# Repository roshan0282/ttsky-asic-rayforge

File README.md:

# How to build the c-implementation of the raytracer

**Option 1: Windows (build.bat)**
1. Ensure MSYS2 UCRT64 is installed at `C:\msys64\ucrt64` with SDL2 installed
2. Navigate to `c-implementation/` folder
3. Run `build.bat` to compile and launch the raytracer

**Option 2: CMake (cross-platform)**
1. Install CMake (3.16+) and SDL2
2. Navigate to `c-implementation/` folder
3. Create a build directory:
   ```bash
   mkdir build && cd build
   cmake ..
   cmake --build . --config Release
   ./raytracer  # or raytracer.exe on Windows
   ```

The raytracer renders a 640×480 scene using Q8.4 fixed-point math and displays it in an SDL2 window.

# How to use verilator-bench to see proper-implementation-no-uart in action
1. Edit `verilator-bench/config.sh`:
   - Set `VERILATOR_SOURCE_FOLDER` to `proper-implementation-no-uart`
   - Set `VERILATOR_TOP_MODULE` to `raytracer_simple`
2. In an MSYS2 UCRT64 terminal, navigate to `verilator-bench/`
3. Run `bash run.sh` to build and launch the raytracer in an SDL window
4. Make sure you have dependencies installed: Verilator, CMake, SDL2, etc.

# How to generate more scenes for the proper-implementation-no-uart
1. go to rayforge.ayannali.net to generate a new scene
2. copy this .sv file and place into scene_lut.sv in proper-implementation-no-uart
3. re-run verilator-bench to see the new scene in action

# Presentation

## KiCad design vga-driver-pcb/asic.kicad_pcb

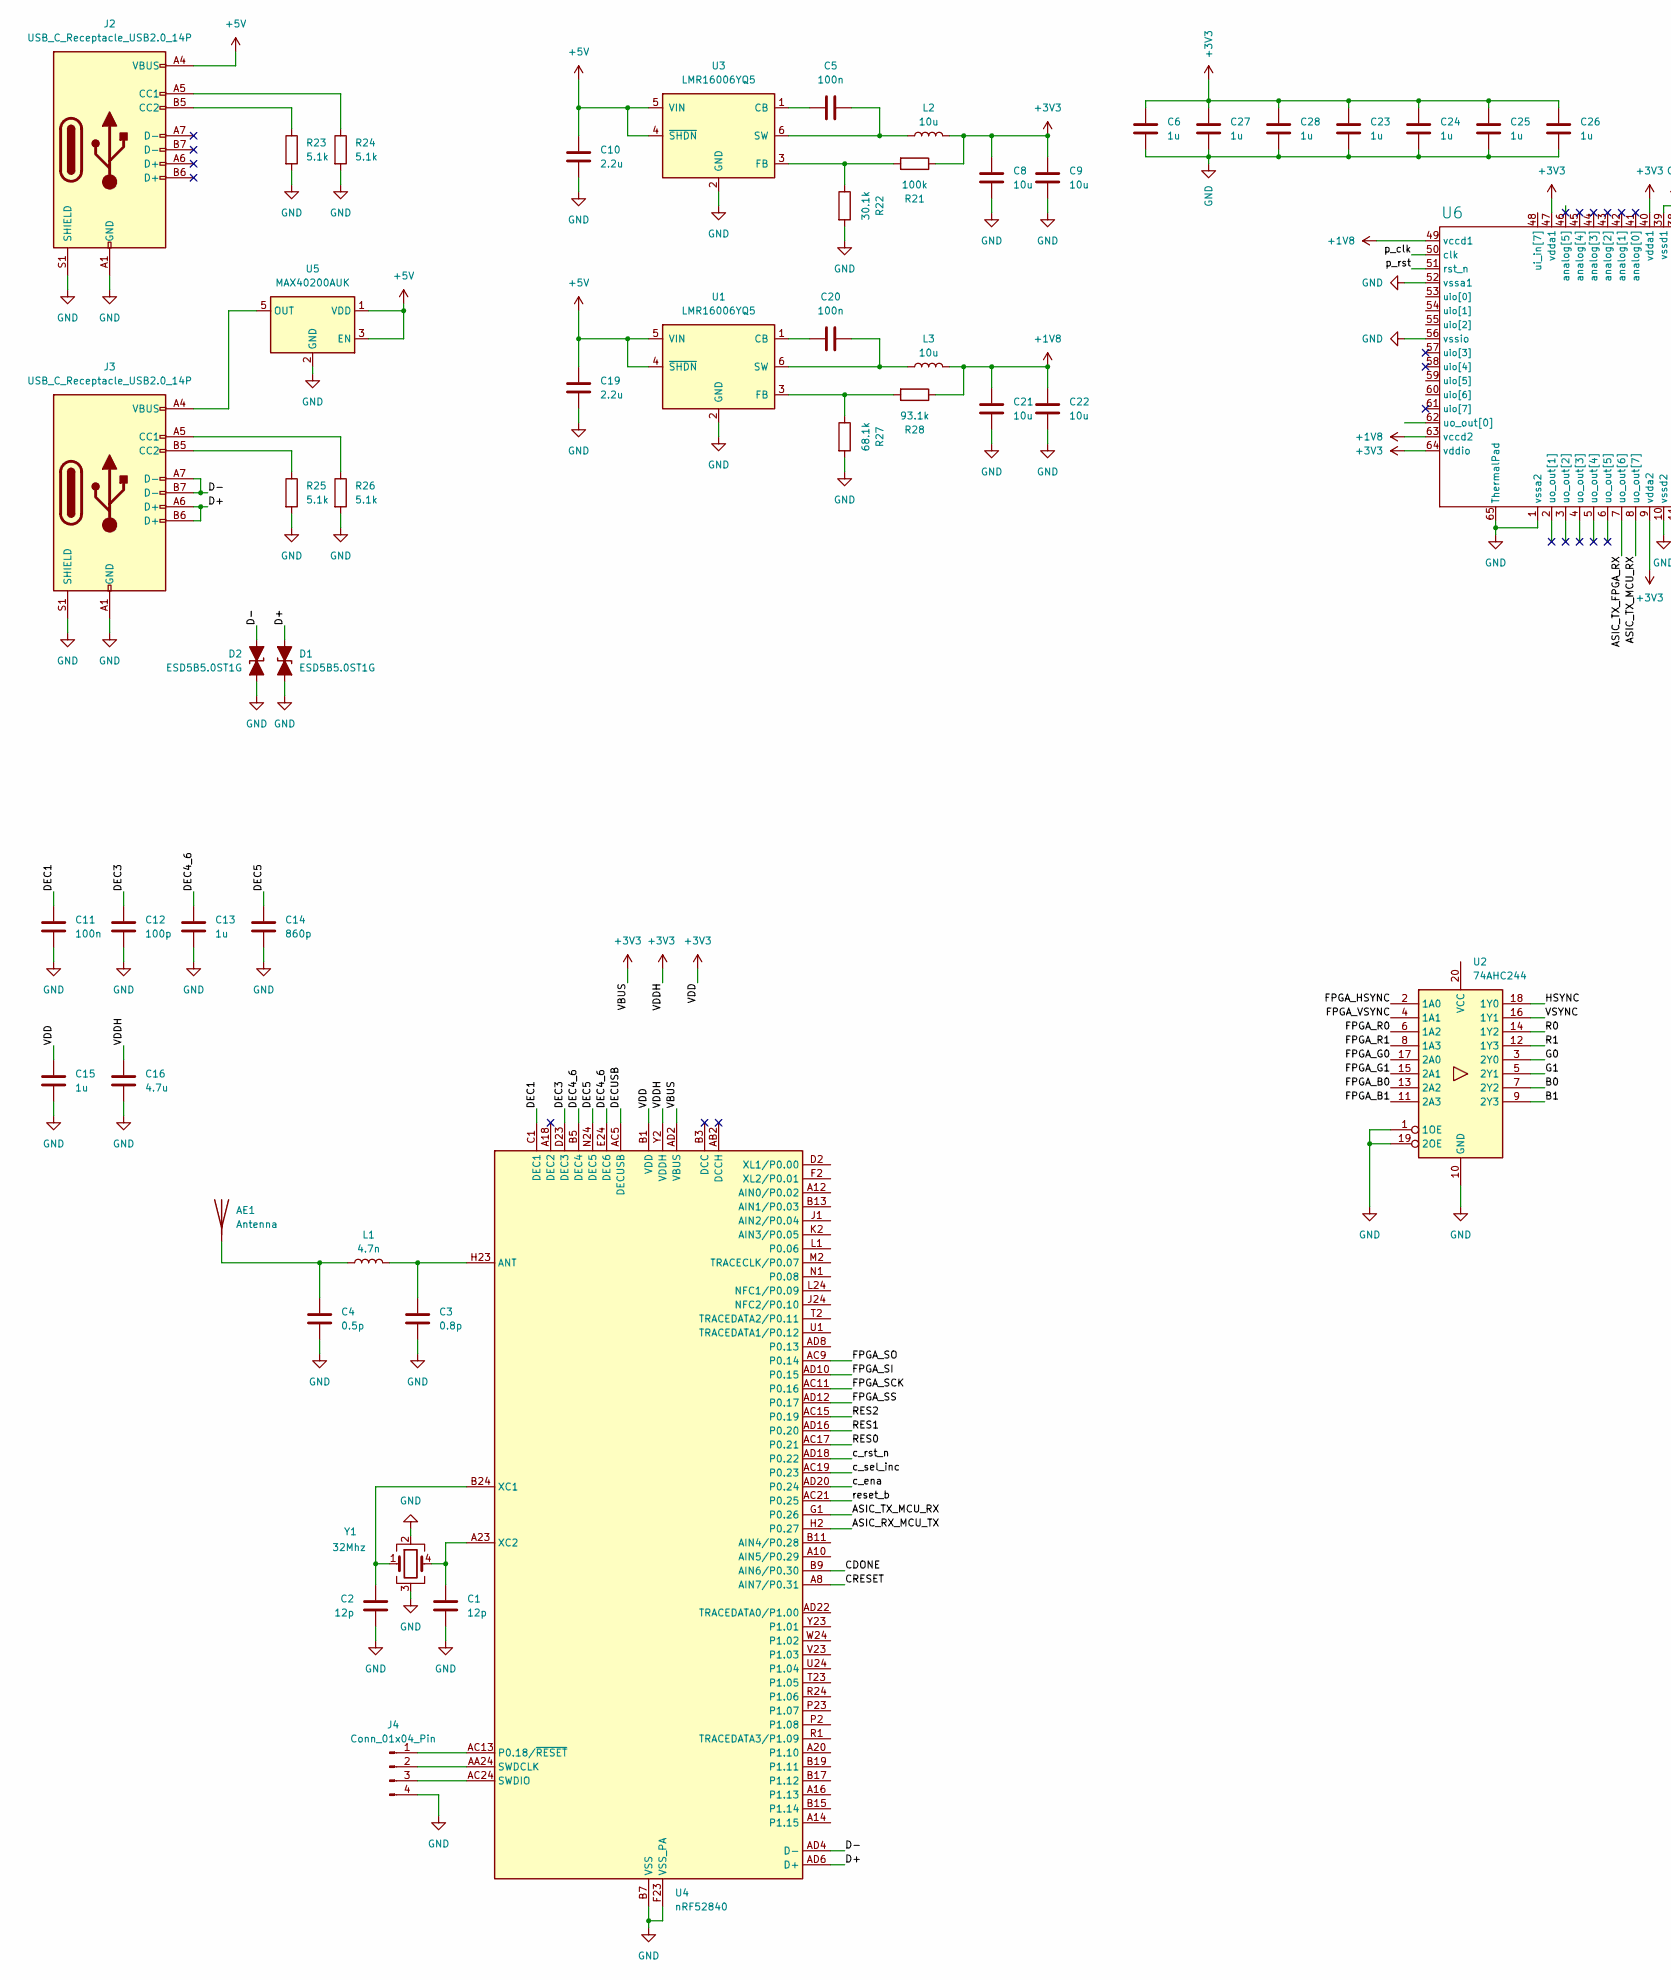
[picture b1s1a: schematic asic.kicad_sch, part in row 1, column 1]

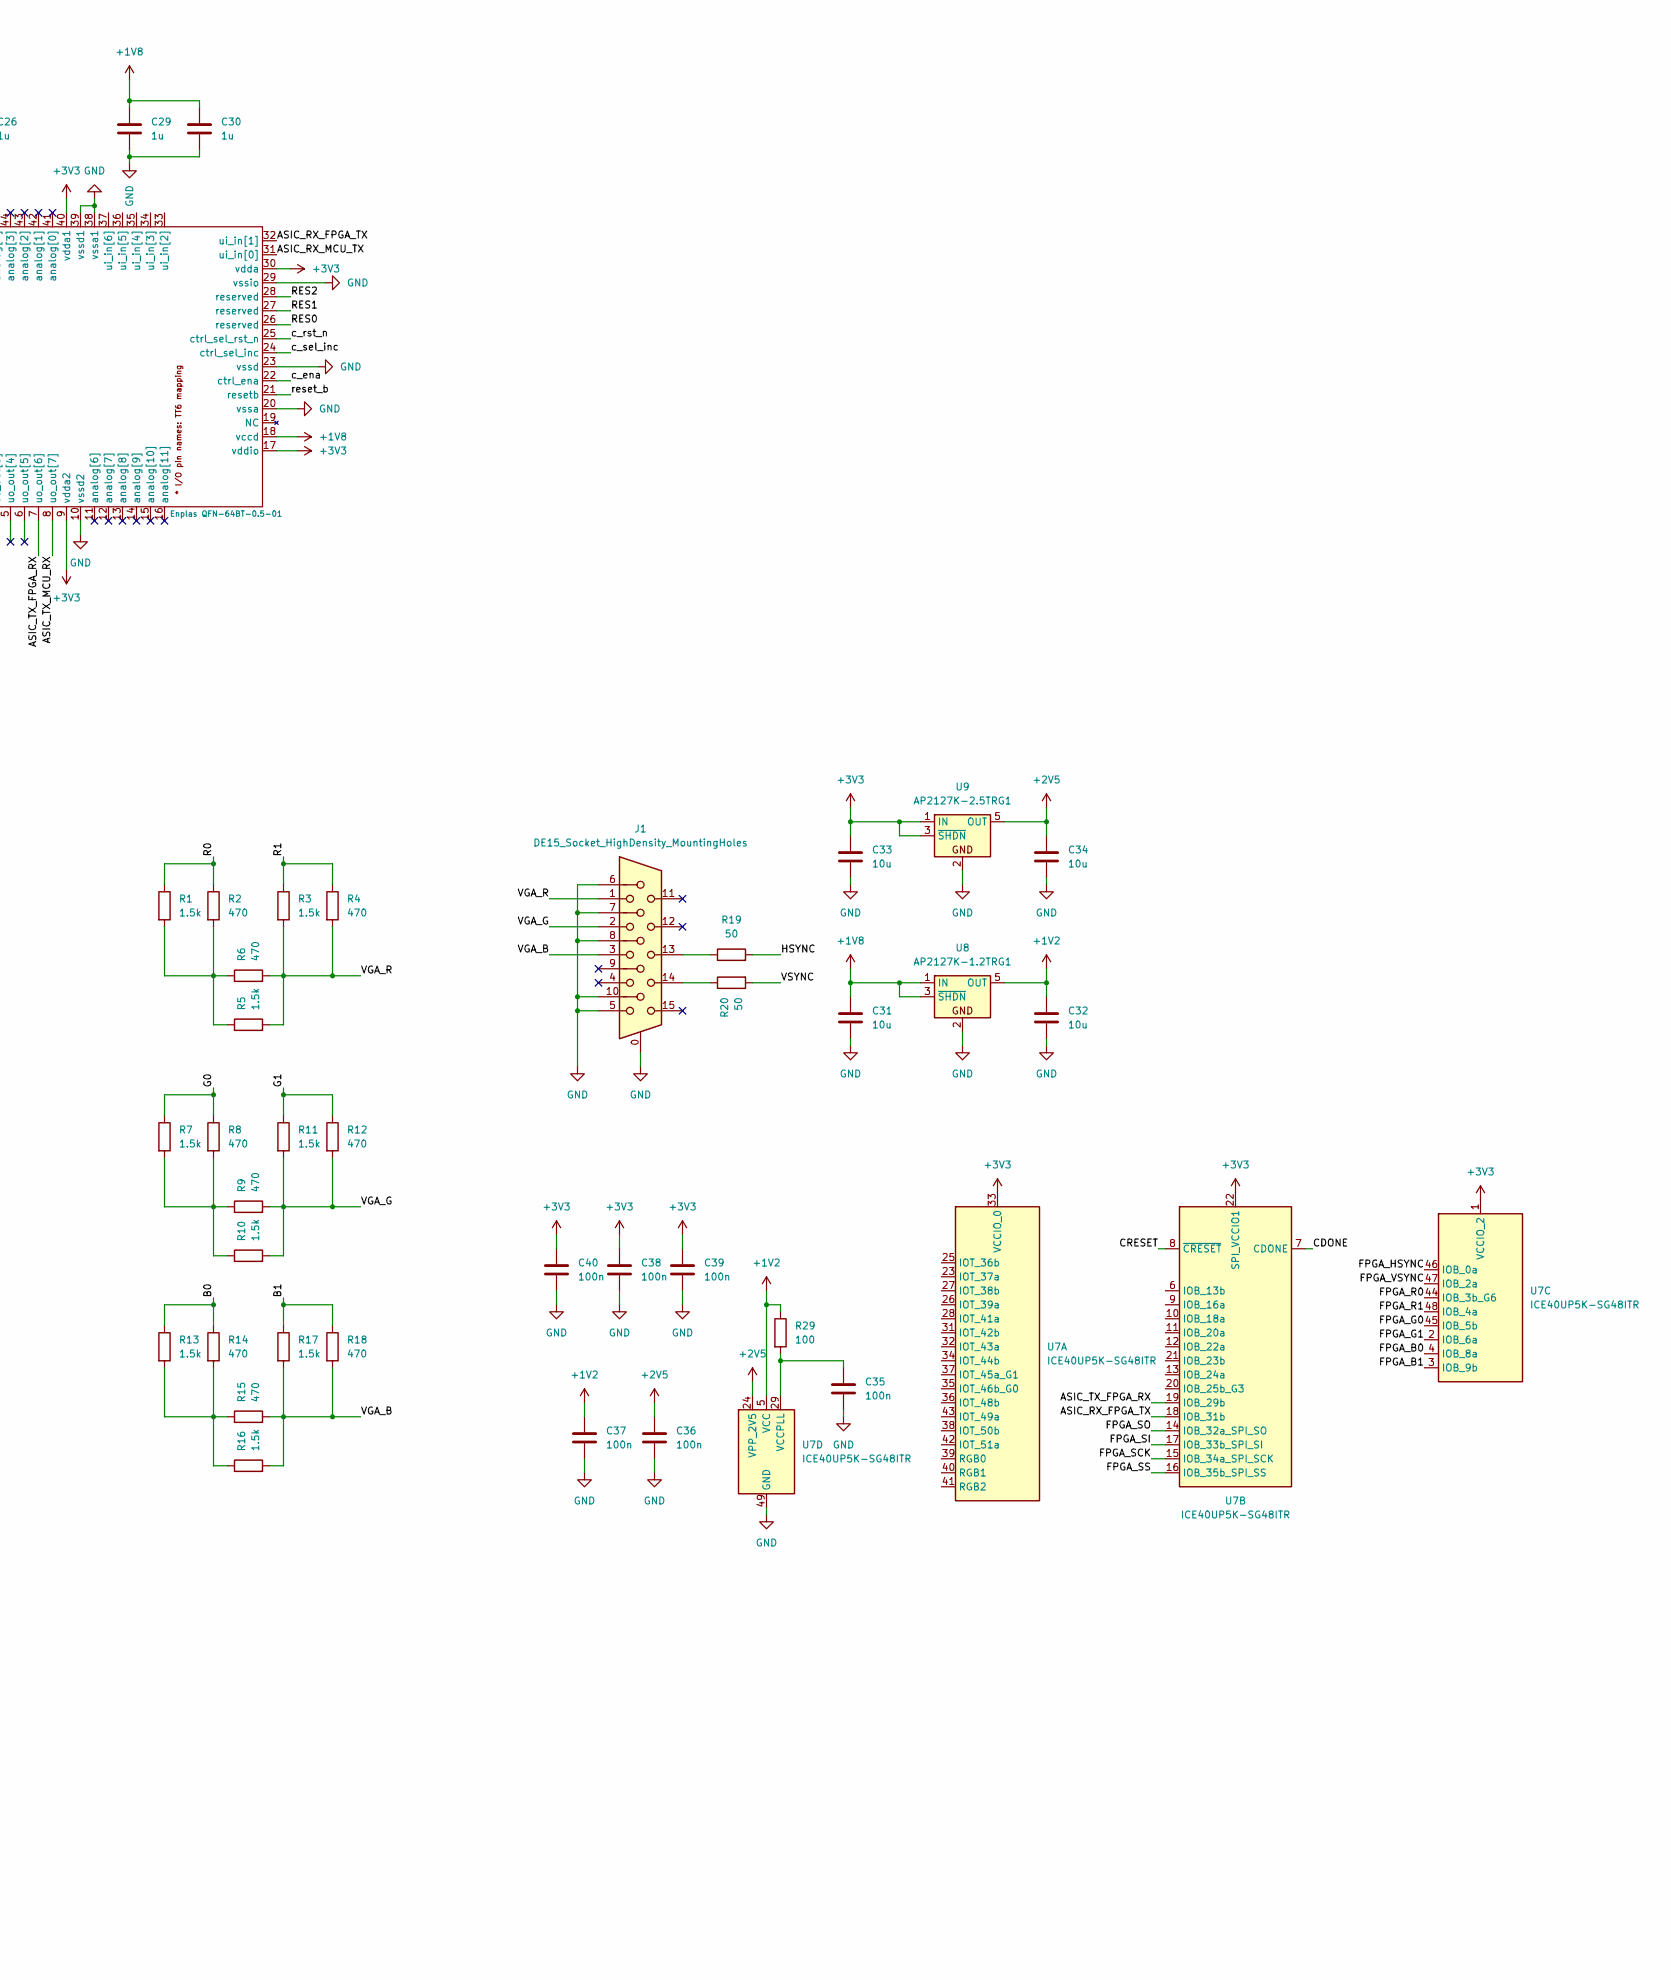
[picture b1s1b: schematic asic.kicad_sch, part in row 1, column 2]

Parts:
AE1: Antenna; Texas_SWRA117D_2.4GHz_Left
C1, C2: 12p; C_0402_1005Metric
C3: 0.8p; C_0402_1005Metric
C4: 0.5p; C_0402_1005Metric
C5, C11, C20, C35, C36, C37, C38, C39, C40: 100n; C_0402_1005Metric
C6, C13, C15, C23, C24, C25, C26, C27, C28, C29, C30: 1u; C_0402_1005Metric
C8, C9, C21, C22, C31, C32, C33, C34: 10u; C_0603_1608Metric
C10, C19: 2.2u; C_0603_1608Metric
C12: 100p; C_0402_1005Metric
C14: 860p; C_0402_1005Metric
C16: 4.7u; C_0402_1005Metric
D1, D2: ESD5B5.0ST1G; D_SOD-523
J1: DE15_Socket_HighDensity_MountingHoles; DSUB-15_Pins_Horizontal_P2.77x2.84mm_EdgePinOffset14.56mm_H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
J2, J3: USB_C_Receptacle_USB2.0_14P; USB_C_Receptacle_GCT_USB4105-xx-A_16P_TopMnt_Horizontal
J4: Conn_01x04_Pin; PinHeader_1x04_P1.00mm_Vertical_SMD_Pin1Left
L1: 4.7n; L_0402_1005Metric
L2, L3: 10u; L_0805_2012Metric
R1, R3, R5, R7, R10, R11, R13, R16, R17: 1.5k; R_0402_1005Metric
R2, R4, R6, R8, R9, R12, R14, R15, R18: 470; R_0402_1005Metric
R19, R20: 50; R_0402_1005Metric
R21: 100k; R_0402_1005Metric
R22: 30.1k; R_0402_1005Metric
R23, R24, R25, R26: 5.1k; R_0402_1005Metric
R27: 68.1k; R_0402_1005Metric
R28: 93.1k; R_0402_1005Metric
R29: 100; R_0402_1005Metric
U1, U3: LMR16006YQ5; SOT-23-6
U2: 74AHC244; WQFN-20-1EP_2.5x4.5mm_P0.5mm_EP1x2.9mm
U4: nRF52840; Nordic_AQFN-73-1EP_7x7mm_P0.5mm
U5: MAX40200AUK; SOT-23-5
U6: Enplas QFN-64BT-0.5-01; QFN-64-1EP_9x9mm_P0.5mm_EP7.3x7.3mm; MPN QFN-64BT-0.5-01
U7: ICE40UP5K-SG48ITR; QFN-48-1EP_7x7mm_P0.5mm_EP5.6x5.6mm
U8: AP2127K-1.2TRG1; SOT-23-5
U9: AP2127K-2.5TRG1; SOT-23-5
Y1: 32Mhz; Crystal_SMD_1210-4Pin_1.2x1.0mm

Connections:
+1V2: C32.2, C37.1, R29.1, U7.5 (VCC), U7.30 (VCC), U8.5 (OUT)
+1V8: C21.2, C22.2, C29.1, C30.1, C31.2, L3.2, R28.1, U6.18 (vccd), U6.49 (vccd1), U6.63 (vccd2), U8.1 (IN), U8.3 (~SHDN)
+2V5: C34.2, C36.1, U7.24 (VPP_2V5), U9.5 (OUT)
+3V3: C6.1, C8.2, C9.2, C15.1, C16.1, C23.1, C24.1, C25.1, C26.1, C27.1, C28.1, C33.2, C38.1, C39.1, C40.1, L2.2, R21.1, U4.A22 (VDD), U4.AD2 (VBUS), U4.AD14 (VDD), U4.AD23 (VDD), U4.B1 (VDD), U4.W1 (VDD), U4.Y2 (VDDH), U6.9 (vdda2), U6.17 (vddio), U6.30 (vdda), U6.40 (vdda1), U6.47 (vdda1), U6.64 (vddio), U7.1 (VCCIO_2), U7.22 (SPI_VCCIO1), U7.33 (VCCIO_0), U9.1 (IN), U9.3 (~SHDN)
+5V: C10.2, C19.2, J2.A4 (VBUS), J2.A9 (VBUS), J2.B4 (VBUS), J2.B9 (VBUS), U1.4 (~SHDN), U1.5 (VIN), U3.4 (~SHDN), U3.5 (VIN), U5.1 (VDD), U5.3 (EN)
/ASIC_RX_FPGA_TX: U6.32 (ui_in[1]), U7.18 (IOB_31b)
/ASIC_RX_MCU_TX: U4.H2 (P0.27), U6.31 (ui_in[0])
/ASIC_TX_FPGA_RX: U6.7 (uo_out[6]), U7.19 (IOB_29b)
/ASIC_TX_MCU_RX: U4.G1 (P0.26), U6.8 (uo_out[7])
/B0: R13.1, R14.1, U2.7 (2Y2)
/B1: R17.1, R18.1, U2.9 (2Y3)
/CDONE: U4.B9 (AIN6/P0.30), U7.7 (CDONE)
/CRESET: U4.A8 (AIN7/P0.31), U7.8 (~CRESET)
/D+: D1.2 (A2), J3.A6 (D+), J3.B6 (D+), U4.AD6 (D+)
/D-: D2.2 (A2), J3.A7 (D-), J3.B7 (D-), U4.AD4 (D-)
/DEC1: C11.1, U4.C1 (DEC1)
/DEC3: C12.1, U4.D23 (DEC3)
/DEC4_6: C13.1, U4.B5 (DEC4), U4.E24 (DEC6)
/DEC5: C14.1, U4.N24 (DEC5)
/DECUSB: U4.AC5 (DECUSB)
/FPGA_B0: U2.13 (2A2), U7.4 (IOB_8a)
/FPGA_B1: U2.11 (2A3), U7.3 (IOB_9b)
/FPGA_G0: U2.17 (2A0), U7.45 (IOB_5b)
/FPGA_G1: U2.15 (2A1), U7.2 (IOB_6a)
/FPGA_HSYNC: U2.2 (1A0), U7.46 (IOB_0a)
/FPGA_R0: U2.6 (1A2), U7.44 (IOB_3b_G6)
/FPGA_R1: U2.8 (1A3), U7.48 (IOB_4a)
/FPGA_SCK: U4.AC11 (P0.16), U7.15 (IOB_34a_SPI_SCK)
/FPGA_SI: U4.AD10 (P0.15), U7.17 (IOB_33b_SPI_SI)
/FPGA_SO: U4.AC9 (P0.14), U7.14 (IOB_32a_SPI_SO)
/FPGA_SS: U4.AD12 (P0.17), U7.16 (IOB_35b_SPI_SS)
/FPGA_VSYNC: U2.4 (1A1), U7.47 (IOB_2a)
/G0: R7.1, R8.1, U2.3 (2Y0)
/G1: R11.1, R12.1, U2.5 (2Y1)
/HSYNC: R19.2, U2.18 (1Y0)
/R0: R1.1, R2.1, U2.14 (1Y2)
/R1: R3.1, R4.1, U2.12 (1Y3)
/RES0: U4.AC17 (P0.21), U6.26 (reserved)
/RES1: U4.AD16 (P0.20), U6.27 (reserved)
/RES2: U4.AC15 (P0.19), U6.28 (reserved)
/VGA_B: J1.3, R15.2, R16.2, R17.2, R18.2
/VGA_G: J1.2, R9.2, R10.2, R11.2, R12.2
/VGA_R: J1.1, R3.2, R4.2, R5.2, R6.2
/VSYNC: R20.2, U2.16 (1Y1)
/c_ena: U4.AD20 (P0.24), U6.22 (ctrl_ena)
/c_rst_n: U4.AD18 (P0.22), U6.25 (ctrl_sel_rst_n)
/c_sel_inc: U4.AC19 (P0.23), U6.24 (ctrl_sel_inc)
/p_clk: U6.50 (clk)
/p_rst: U6.51 (rst_n)
/reset_b: U4.AC21 (P0.25), U6.21 (resetb)
GND: C1.2, C2.2, C3.2, C4.2, C6.2, C8.1, C9.1, C10.1, C11.2, C12.2, C13.2, C14.2, C15.2, C16.2, C19.1, C21.1, C22.1, C23.2, C24.2, C25.2, C26.2, C27.2, C28.2, C29.2, C30.2, C31.1, C32.1, C33.1, C34.1, C35.2, C36.2, C37.2, C38.2, C39.2, C40.2, D1.1 (A1), D2.1 (A1), J1.0, J1.5, J1.6, J1.7, J1.8, J1.10, J2.A1 (GND), J2.A12 (GND), J2.B1 (GND), J2.B12 (GND), J2.S1 (SHIELD), J3.A1 (GND), J3.A12 (GND), J3.B1 (GND), J3.B12 (GND), J3.S1 (SHIELD), J4.4, R22.2, R23.2, R24.2, R25.2, R26.2, R27.2, U1.2 (GND), U2.1 (1OE), U2.10 (GND), U2.19 (2OE), U3.2 (GND), U4.B7 (VSS), U4.EP (VSS), U4.F23 (VSS_PA), U5.2 (GND), U6.1 (vssa2), U6.10 (vssd2), U6.20 (vssa), U6.23 (vssd), U6.29 (vssio), U6.38 (vssa1), U6.39 (vssd1), U6.52 (vssa1), U6.56 (vssio), U6.65 (ThermalPad), U7.49 (GND), U8.2, U9.2, Y1.2, Y1.3
unnamed: AE1.1 (A), C4.1, L1.1
unnamed: J1.13, R19.1
unnamed: J1.14, R20.1
unnamed: J2.A5 (CC1), R24.1
unnamed: J2.B5 (CC2), R23.1
unnamed: J3.A5 (CC1), R26.1
unnamed: J3.B5 (CC2), R25.1
unnamed: J4.1, U4.AC13 (P0.18/~RESET)
unnamed: J4.2, U4.AA24 (SWDCLK)
unnamed: J4.3, U4.AC24 (SWDIO)
unnamed: R1.2, R2.2, R5.1, R6.1
unnamed: R7.2, R8.2, R9.1, R10.1
unnamed: R13.2, R14.2, R15.1, R16.1
unnamed: C20.1, U1.1 (CB)
unnamed: R27.1, R28.2, U1.3 (FB)
unnamed: C20.2, L3.1, U1.6 (SW)
unnamed: C5.1, U3.1 (CB)
unnamed: R21.2, R22.1, U3.3 (FB)
unnamed: C5.2, L2.1, U3.6 (SW)
unnamed: C3.1, L1.2, U4.H23 (ANT)
unnamed: C2.1, U4.B24 (XC1), Y1.1
unnamed: C1.1, U4.A23 (XC2), Y1.4
unnamed: J3.A4 (VBUS), J3.A9 (VBUS), J3.B4 (VBUS), J3.B9 (VBUS), U5.5 (OUT)
unnamed: C35.1, R29.2, U7.29 (VCCPLL)

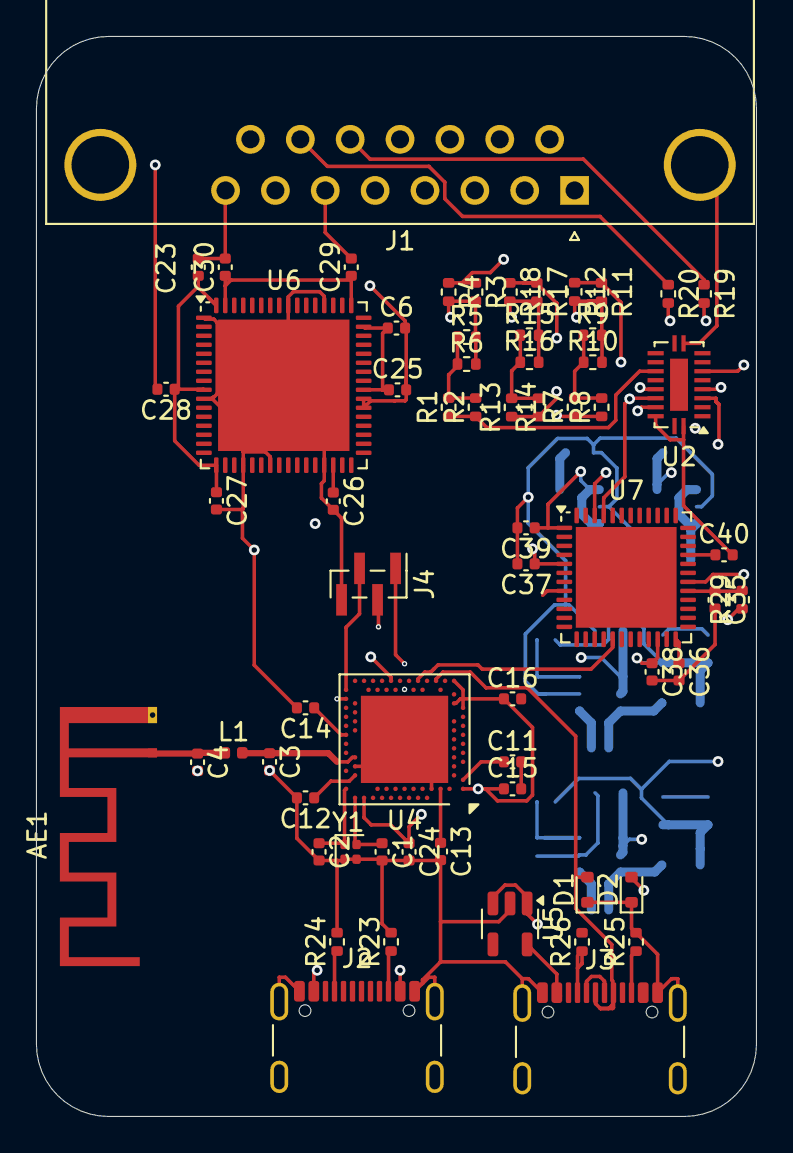
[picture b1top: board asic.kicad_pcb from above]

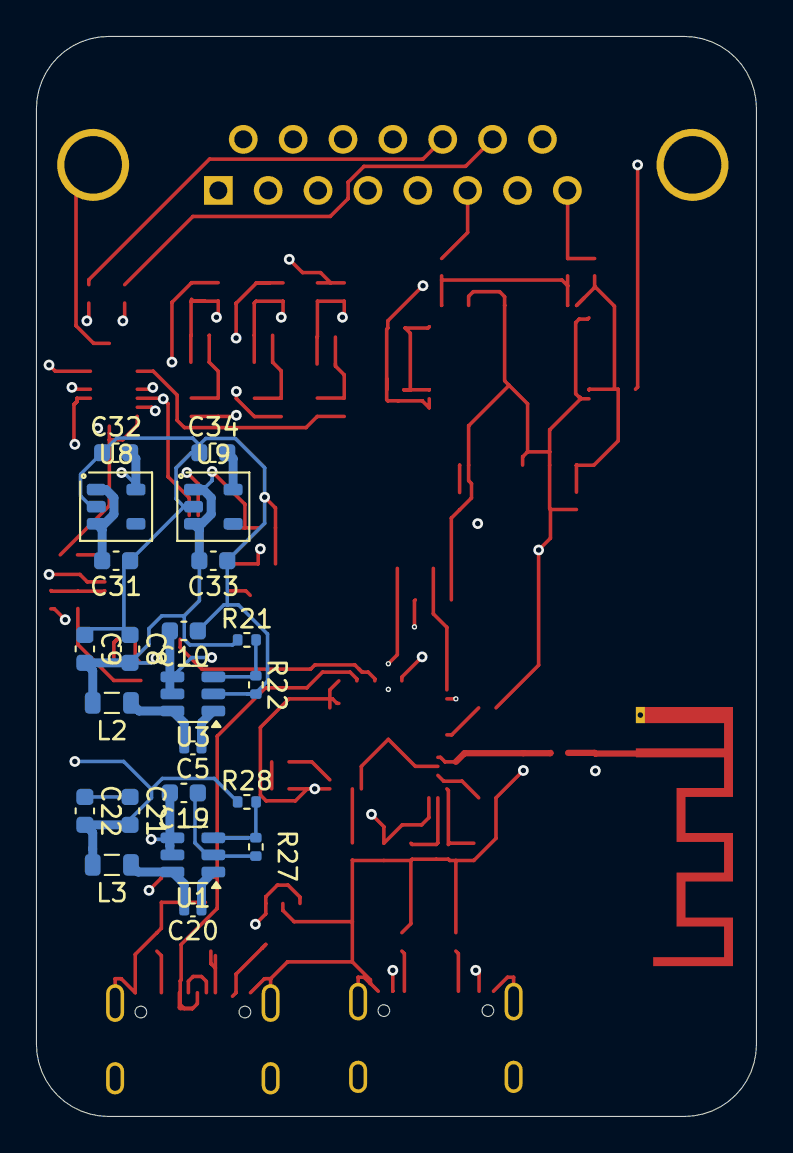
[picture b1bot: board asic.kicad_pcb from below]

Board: 6 copper layers, 40.0 x 60.0 mm, 86 parts (22 on the bottom side), 72 nets.

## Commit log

2026-02-16 Remove simproc_system instantiation from tt_um_asic
    Removed instantiation of simproc_system module.
2026-02-16 deleted rubbish
2026-02-16 add the verilator-view
2026-02-16 bla bla bla
2026-02-16 fixed docs
2026-02-16 fixed language
2026-02-16 changed to verilog
2026-02-16 fixes for the verialtor-bench stuff
2026-02-16 vga test
2026-02-16 random fix
2026-02-16 finalized the generic testbench for verialtor
2026-02-16 comment changes
2026-02-17 make sure to use the proper vga timing!
2026-02-17 rotating background and text test
2026-02-17 test the new text stuff3
2026-02-17 test the new text stuff4
2026-02-17 remove old files
2026-02-17 Added primitive floating point operations to pipeline.md
2026-02-17 Outlined 2.3 and 2.4 in pipeline.md
2026-02-17 begin raytracing
2026-02-17 move to imple folder
2026-02-17 add in the placeholder code
2026-02-17 add todos
2026-02-18 Modified fixed_point_mul in primitives.v
2026-02-18 Modified fixed_point_sqrt and created fixed_point_sqrt_pipe in primitives.v
2026-02-18 243 code
2026-02-18 fixed todos
2026-02-18 synthesis test fixed branch declarations
2026-02-18 Created UART modules
2026-02-18 cordic vector normalization - not working yet almost there
2026-02-22 finally working
2026-02-22 Commented out assert in test.py
2026-02-22 Modified tb.v to have correct module name
2026-02-22 Added swap file to give runner more memory for test.yaml
2026-02-22 Trying pre-built binary to install verilator
2026-02-22 Changed makefile back to icarus
2026-02-22 stuff
2026-02-22 Refactor ray-sphere intersection module for 32-bit inputs
2026-02-22 Refactor fixed point modules to Q16.16 format
2026-02-22 change icarus to systemveirlog
2026-02-22 change icarus back to verilog
2026-02-22 fixed declaration
2026-02-22 comma
2026-02-22 moved package inside top
2026-02-22 Created uartSceneReceiver.sv
2026-02-22 Removed LUT from raytracer-simple.sv
2026-02-22 fixed break
2026-02-22 fixed relfx
2026-02-22 json
2026-02-22 chonk
2026-02-22 fix latch
2026-02-22 info.md
2026-02-22 all code working now
2026-02-22 final branch
2026-02-22 add pcb
2026-02-22 green checkmark
2026-02-22 update docs
